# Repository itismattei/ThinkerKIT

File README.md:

# ThinkerKIT
ridefinisce le caratteristiche della scheda thinkerkit

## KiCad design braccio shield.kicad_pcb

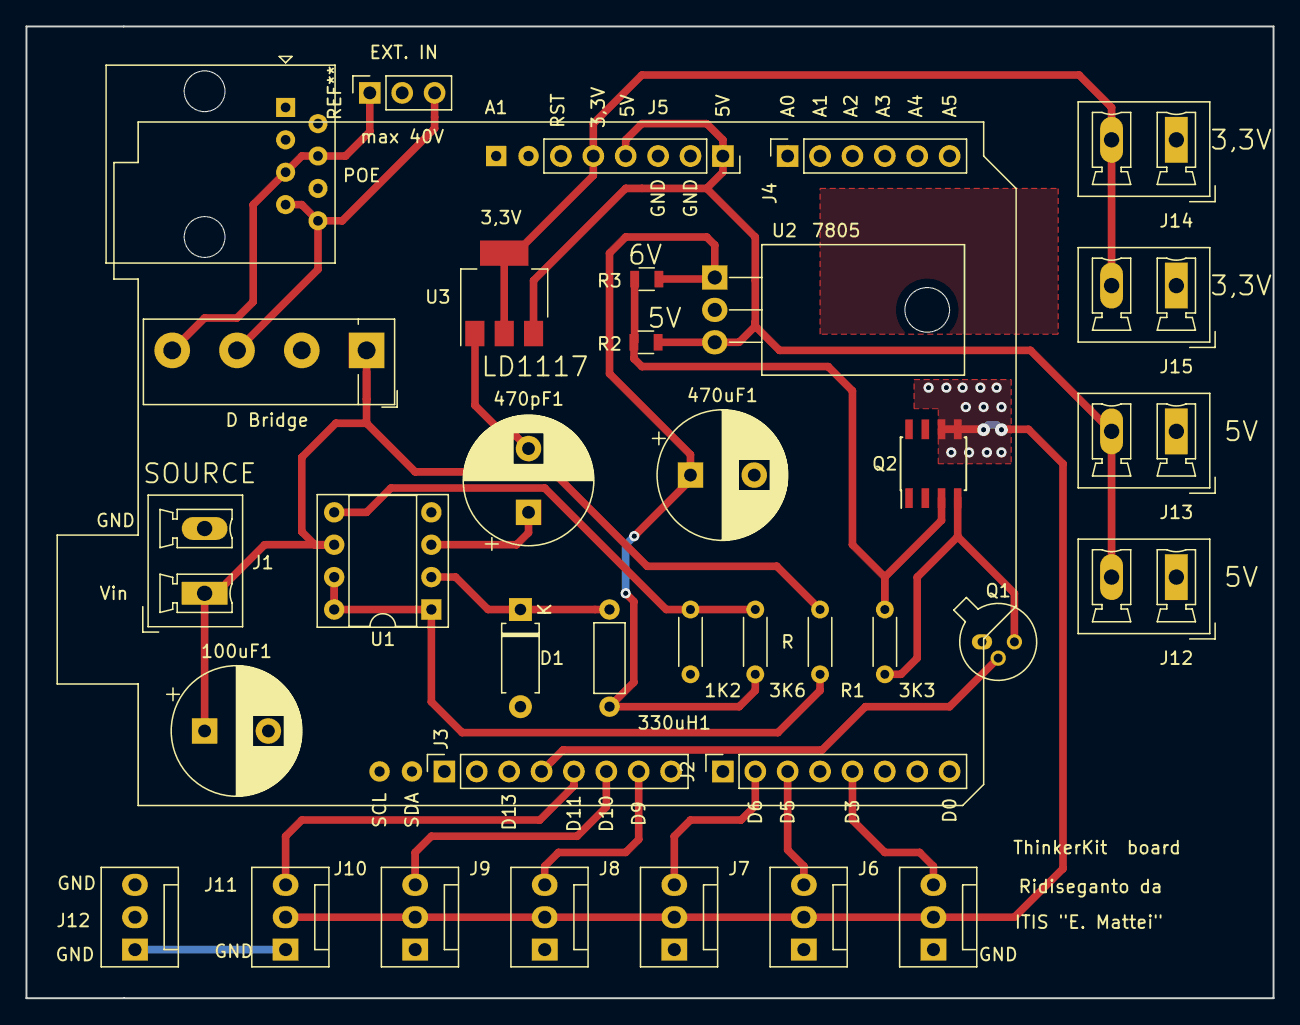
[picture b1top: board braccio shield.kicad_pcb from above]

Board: 2 copper layers, 97.8 x 76.2 mm, 35 parts (0 on the bottom side), 36 nets.

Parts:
1K2, 3K3, 3K6: R; R_Axial_DIN0204_L3.6mm_D1.6mm_P5.08mm_Horizontal
100uF1, 470pF1, 470uF1: CP1; CP_Radial_D10.0mm_P5.00mm
330uH1: L_Core_Iron; L_Axial_L5.3mm_D2.2mm_P7.62mm_Horizontal_Vishay_IM-1
A1: Arduino_UNO_R3
D1: D_Schottky; D_A-405_P7.62mm_Horizontal
D Bridge: D_Bridge_+-AA; Diode_Bridge_Vishay_KBL
J1: Alimentazione; PhoenixContact_MCV_1,5_2-G-5.08_1x02_P5.08mm_Vertical
J2, J3: Conn_01x08_Male; PinSocket_1x08_P2.54mm_Vertical
J4, J5: Conn_01x06_Male; PinSocket_1x06_P2.54mm_Vertical
J6, J7, J8, J9, J10, J11, J12: Conn_01x03_Male; FanPinHeader_1x03_P2.54mm_Vertical
J12#2, J13: 5V; PhoenixContact_MCV_1,5_2-G-5.08_1x02_P5.08mm_Vertical
J14, J15: 3,3V; PhoenixContact_MCV_1,5_2-G-5.08_1x02_P5.08mm_Vertical
POE: RJ45; RJ45_Amphenol_54602-x08_Horizontal
Q1: BC107; TO-18-3
Q2: IRF7309IPBF; SOIC-8_3.9x4.9mm_P1.27mm
R1: 300; R_Axial_DIN0204_L3.6mm_D1.6mm_P5.08mm_Horizontal
R2, R3: R_0805
U1: MC34063AP; DIP-8_W7.62mm_Socket
U2: L7805; TO-220-3_Horizontal_TabDown
U3: LD1117S33TR_SOT223; SOT-223-3_TabPin2

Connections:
3,3V: A1.4, J5.5, J14.2, J15.2, U3.2
5V: A1.5, A1.8, J5.1, J5.4, J12#2.2, J13.2, R2.2, U2.3, U3.3
5Vb: J6.2, J7.2, J8.2, J9.2, J10.2, J11.2, Q2.5, Q2.6
6V: 3K6.1, 330uH1.2, 470uF1.1, R3.2, U2.1
/VN: D Bridge.4, POE.4, POE.5
/VP: D Bridge.3, POE.7, POE.8
A0: A1.9, J4.1
A1: A1.10, J4.2
A2: A1.11, J4.3
A3: A1.12, J4.4
A4: A1.13, J4.5
A5: A1.14, J4.6
AREF: A1.30, J3.1
D0: A1.15, J2.8
D1: A1.16, J2.7
D2: A1.17, J2.6
D3: A1.18, J2.5, J6.3
D4: A1.19, J2.4
D5: A1.20, J2.3, J7.3
D6: A1.21, J2.2, J8.3
D7: A1.22, J2.1
D8: A1.23, J3.8
D9: A1.24, J3.7, J9.3
D10: A1.25, J3.6, J10.3
D11: A1.26, J3.5, J11.3
D12: A1.27, J3.4, Q1.2
D13: A1.28, J3.3
GND: 1K2.2, 100uF1.2, 470pF1.2, 470uF1.2, A1.6, A1.7, A1.29, D1.2, D Bridge.2, J1.2, J3.2, J5.2, J5.3, J6.1, J7.1, J8.1, J9.1, J10.1, J11.1, J12.1, J12.3, J12#2.1, J13.1, J14.1, J15.1, Q1.1, U1.4, U2.2, U3.1
unnamed: 1K2.1, 3K6.2, U1.5
unnamed: 3K3.1, Q1.3, Q2.4
unnamed: 3K3.2, Q2.3, R2.1, R3.1
unnamed: 330uH1.1, D1.1, U1.2
unnamed: 470pF1.1, U1.3
unnamed: R1.1, U1.1, U1.7, U1.8
RESET: A1.3, J5.6
Vin: 100uF1.1, D Bridge.1, J1.1, R1.2, U1.6

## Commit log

2019-10-06 First commit
    Schema elettrico della scheda ThinkerKit modificata e migliorata.
